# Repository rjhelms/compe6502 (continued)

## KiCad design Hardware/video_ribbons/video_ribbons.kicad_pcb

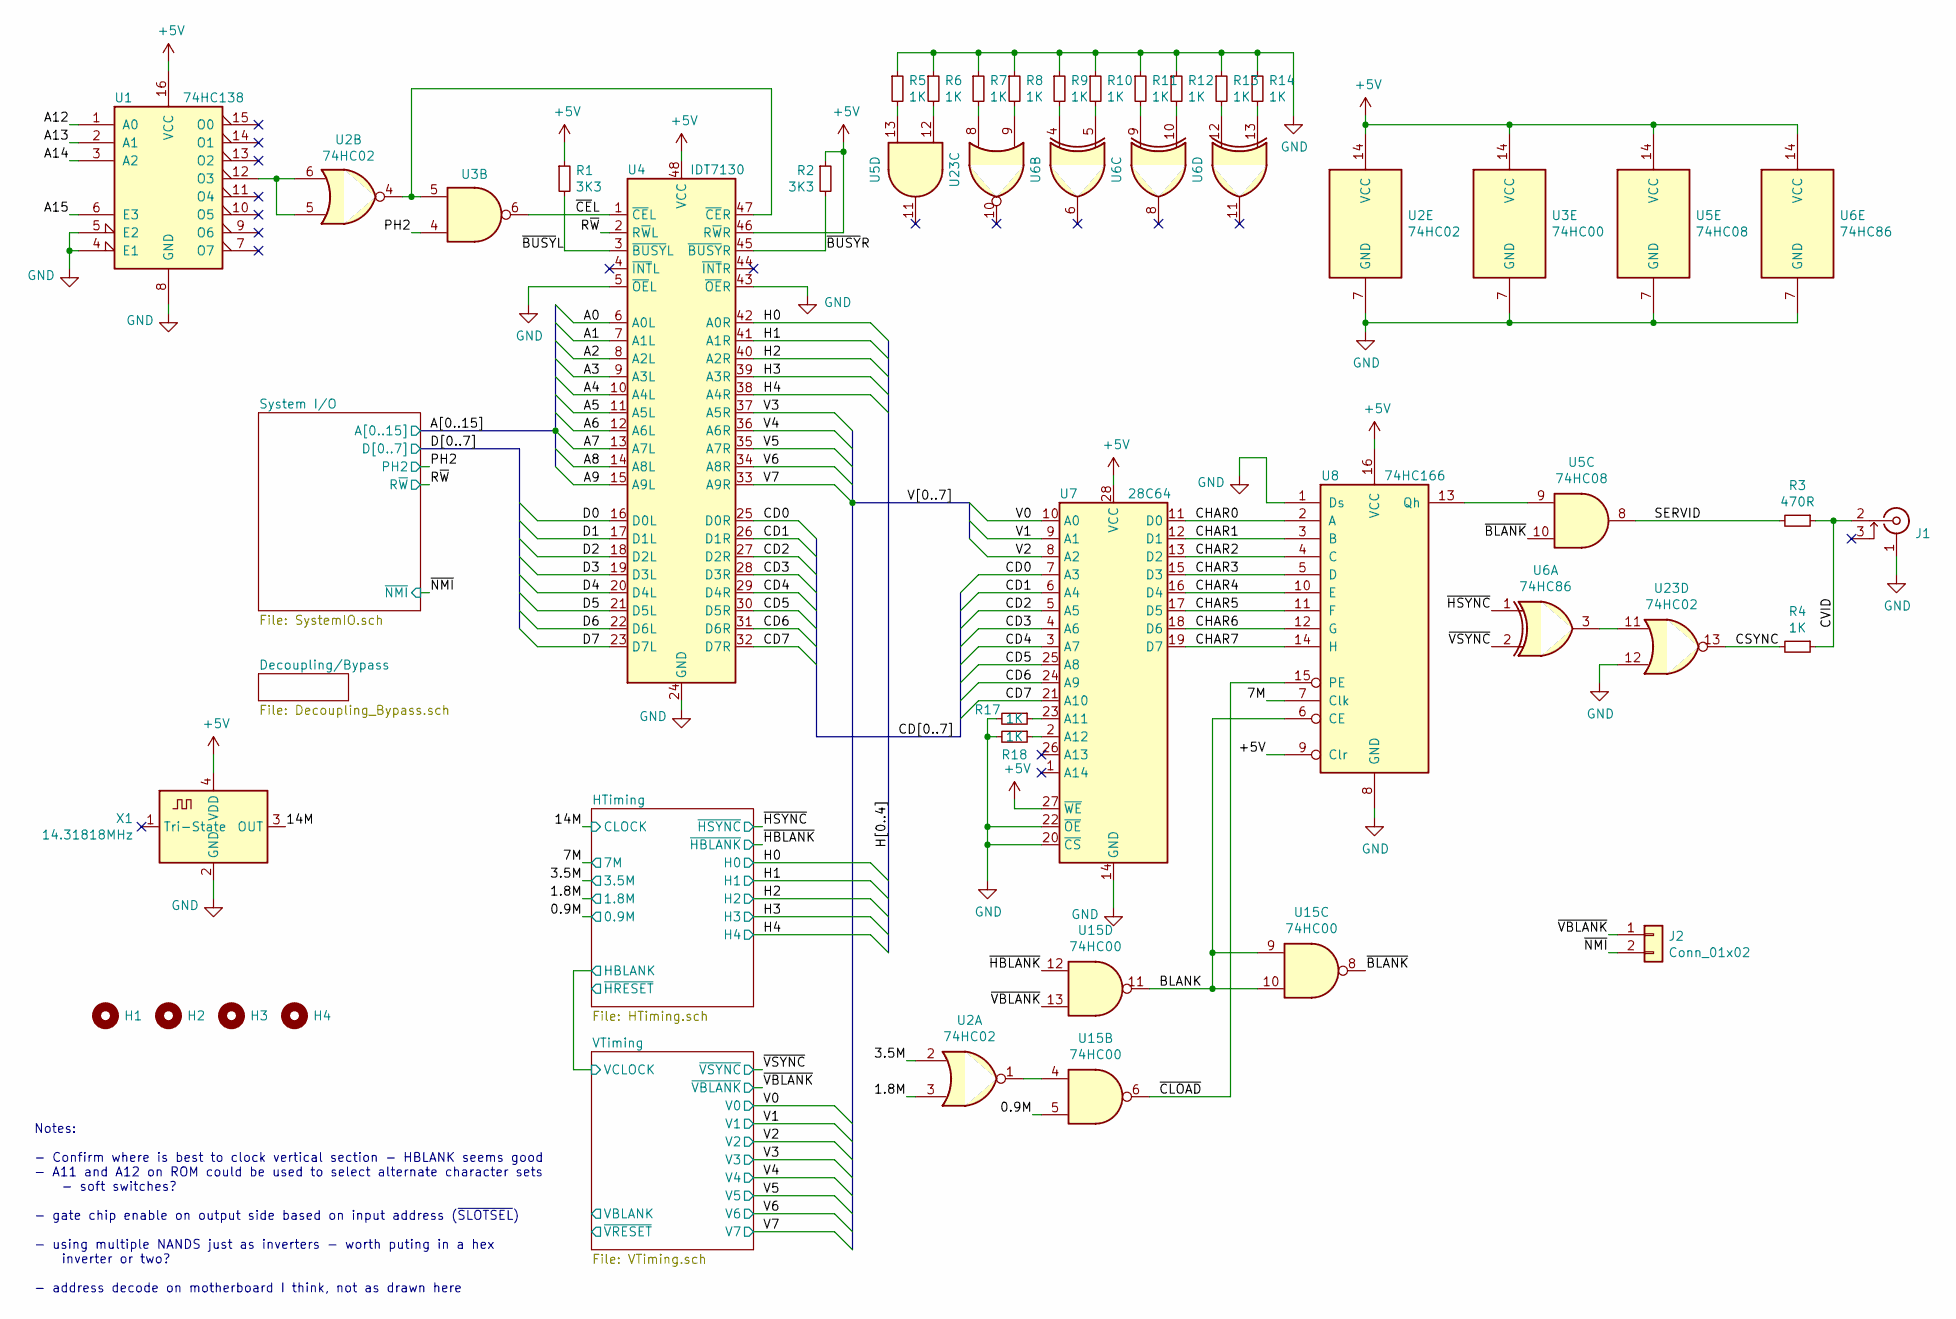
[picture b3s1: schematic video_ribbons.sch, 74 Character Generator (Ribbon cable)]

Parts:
H1, H2, H3, H4: MountingHole; MountingHole_3.2mm_M3
J1: Conn_Coaxial_Sleeve_Pin2Tip; Jack_RCA_Switchcraft_PJRAN1X1UxxX
J2: Conn_01x02; PinHeader_1x02_P2.54mm_Vertical
R1, R2: 3K3; R_0805_2012Metric
R3: 470R; R_0805_2012Metric
R4, R5, R6, R7, R8, R9, R10, R11, R12, R13, R14, R17, R18: 1K; R_0805_2012Metric
U1: 74HC138; SOIC-16_3.9x9.9mm_P1.27mm
U2, U23: 74HC02; SOIC-14_3.9x8.7mm_P1.27mm
U3, U15: 74HC00; SOIC-14_3.9x8.7mm_P1.27mm
U4: IDT7130; DIP-48_W15.24mm_Socket_LongPads
U5: 74HC08; SOIC-14_3.9x8.7mm_P1.27mm
U6: 74HC86; SOIC-14_3.9x8.7mm_P1.27mm
U7: 28C64; DIP-28_W15.24mm_Socket_LongPads
U8: 74HC166; SOIC-16_3.9x9.9mm_P1.27mm
X1: 14.31818MHz; Oscillator_SMD_IQD_IQXO70-4Pin_7.5x5.0mm

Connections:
+5V: R1.1, R2.1, U1.16 (VCC), U2.14 (VCC), U3.14 (VCC), U4.46 (R~W~R), U4.48 (VCC), U5.14 (VCC), U6.14 (VCC), U7.27 (~WE), U7.28 (VCC), U8.9 (Clr), U8.16 (VCC), X1.4 (VDD); also elsewhere on the board
/0.9M: U15.5; also elsewhere on the board
/1.8M: U2.3; also elsewhere on the board
/3.5M: U2.2; also elsewhere on the board
/7M: U8.7 (Clk); also elsewhere on the board
/14M: X1.3 (OUT); also elsewhere on the board
/A0: U4.6 (A0L); also elsewhere on the board
/A1: U4.7 (A1L); also elsewhere on the board
/A2: U4.8 (A2L); also elsewhere on the board
/A3: U4.9 (A3L); also elsewhere on the board
/A4: U4.10 (A4L); also elsewhere on the board
/A5: U4.11 (A5L); also elsewhere on the board
/A6: U4.12 (A6L); also elsewhere on the board
/A7: U4.13 (A7L); also elsewhere on the board
/A8: U4.14 (A8L); also elsewhere on the board
/A9: U4.15 (A9L); also elsewhere on the board
/A12: U1.1 (A0); also elsewhere on the board
/A13: U1.2 (A1); also elsewhere on the board
/A14: U1.3 (A2); also elsewhere on the board
/A15: U1.6 (E3); also elsewhere on the board
/BLANK: U8.6 (CE), U15.9, U15.10, U15.11
/CD0: U4.25 (D0R), U7.7 (A3)
/CD1: U4.26 (D1R), U7.6 (A4)
/CD2: U4.27 (D2R), U7.5 (A5)
/CD3: U4.28 (D3R), U7.4 (A6)
/CD4: U4.29 (D4R), U7.3 (A7)
/CD5: U4.30 (D5R), U7.25 (A8)
/CD6: U4.31 (D6R), U7.24 (A9)
/CD7: U4.32 (D7R), U7.21 (A10)
/CHAR0: U7.11 (D0), U8.2 (A)
/CHAR1: U7.12 (D1), U8.3 (B)
/CHAR2: U7.13 (D2), U8.4 (C)
/CHAR3: U7.15 (D3), U8.5 (D)
/CHAR4: U7.16 (D4), U8.10 (E)
/CHAR5: U7.17 (D5), U8.11 (F)
/CHAR6: U7.18 (D6), U8.12 (G)
/CHAR7: U7.19 (D7), U8.14 (H)
/CSYNC: R4.2, U23.13
/CVID: J1.2 (In), R3.1, R4.1
/D0: U4.16 (D0L); also elsewhere on the board
/D1: U4.17 (D1L); also elsewhere on the board
/D2: U4.18 (D2L); also elsewhere on the board
/D3: U4.19 (D3L); also elsewhere on the board
/D4: U4.20 (D4L); also elsewhere on the board
/D5: U4.21 (D5L); also elsewhere on the board
/D6: U4.22 (D6L); also elsewhere on the board
/D7: U4.23 (D7L); also elsewhere on the board
/H0: U4.42 (A0R); also elsewhere on the board
/H1: U4.41 (A1R); also elsewhere on the board
/H2: U4.40 (A2R); also elsewhere on the board
/H3: U4.39 (A3R); also elsewhere on the board
/H4: U4.38 (A4R); also elsewhere on the board
/PH2: U3.4; also elsewhere on the board
/R~W: U4.2 (R~W~L); also elsewhere on the board
/SERVID: R3.2, U5.8
/V0: U7.10 (A0); also elsewhere on the board
/V1: U7.9 (A1); also elsewhere on the board
/V2: U7.8 (A2); also elsewhere on the board
/V3: U4.37 (A5R); also elsewhere on the board
/V4: U4.36 (A6R); also elsewhere on the board
/V5: U4.35 (A7R); also elsewhere on the board
/V6: U4.34 (A8R); also elsewhere on the board
/V7: U4.33 (A9R); also elsewhere on the board
/~BLANK: U5.10, U15.8
/~BUSY~L: R1.2, U4.3 (~BUSY~L)
/~BUSY~R: R2.2, U4.45 (~BUSY~R)
/~CE~L: U3.6, U4.1 (~CE~L)
/~CLOAD: U8.15 (PE), U15.6
/~HBLANK: U15.12; also elsewhere on the board
/~HSYNC: U6.1; also elsewhere on the board
/~NMI: J2.2; also elsewhere on the board
/~VBLANK: J2.1, U15.13; also elsewhere on the board
/~VSYNC: U6.2; also elsewhere on the board
GND: J1.1 (Ext), R5.1, R6.1, R7.1, R8.1, R9.1, R10.1, R11.1, R12.1, R13.1, R14.1, R17.2, R18.2, U1.4 (E1), U1.5 (E2), U1.8 (GND), U2.7 (GND), U3.7 (GND), U4.5 (~OE~L), U4.24 (GND), U4.43 (~OE~R), U5.7 (GND), U6.7 (GND), U7.14 (GND), U7.20 (~CS), U7.22 (~OE), U8.1 (Ds), U8.8 (GND), U23.12, X1.2 (GND); also elsewhere on the board
unnamed: R5.2, U5.13
unnamed: R6.2, U5.12
unnamed: R7.2, U23.8
unnamed: R8.2, U23.9
unnamed: R9.2, U6.4
unnamed: R10.2, U6.5
unnamed: R11.2, U6.9
unnamed: R12.2, U6.10
unnamed: R13.2, U6.12
unnamed: R14.2, U6.13
unnamed: R17.1, U7.23 (A11)
unnamed: R18.1, U7.2 (A12)
unnamed: U1.12 (O3), U2.5, U2.6
unnamed: U2.4, U3.5, U4.47 (~CE~R)
unnamed: U5.9, U8.13 (Qh)
unnamed: U2.1, U15.4
unnamed: U6.3, U23.11

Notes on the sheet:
Notes: - Confirm where is best to clock vertical section - HBLANK seems good - A11 and A12 on ROM could be used to select alternate character sets - soft switches? - gate chip enable on output side based on input address (~SLOTSEL~) - using multiple NANDS just as inverters - worth puting in a hex i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

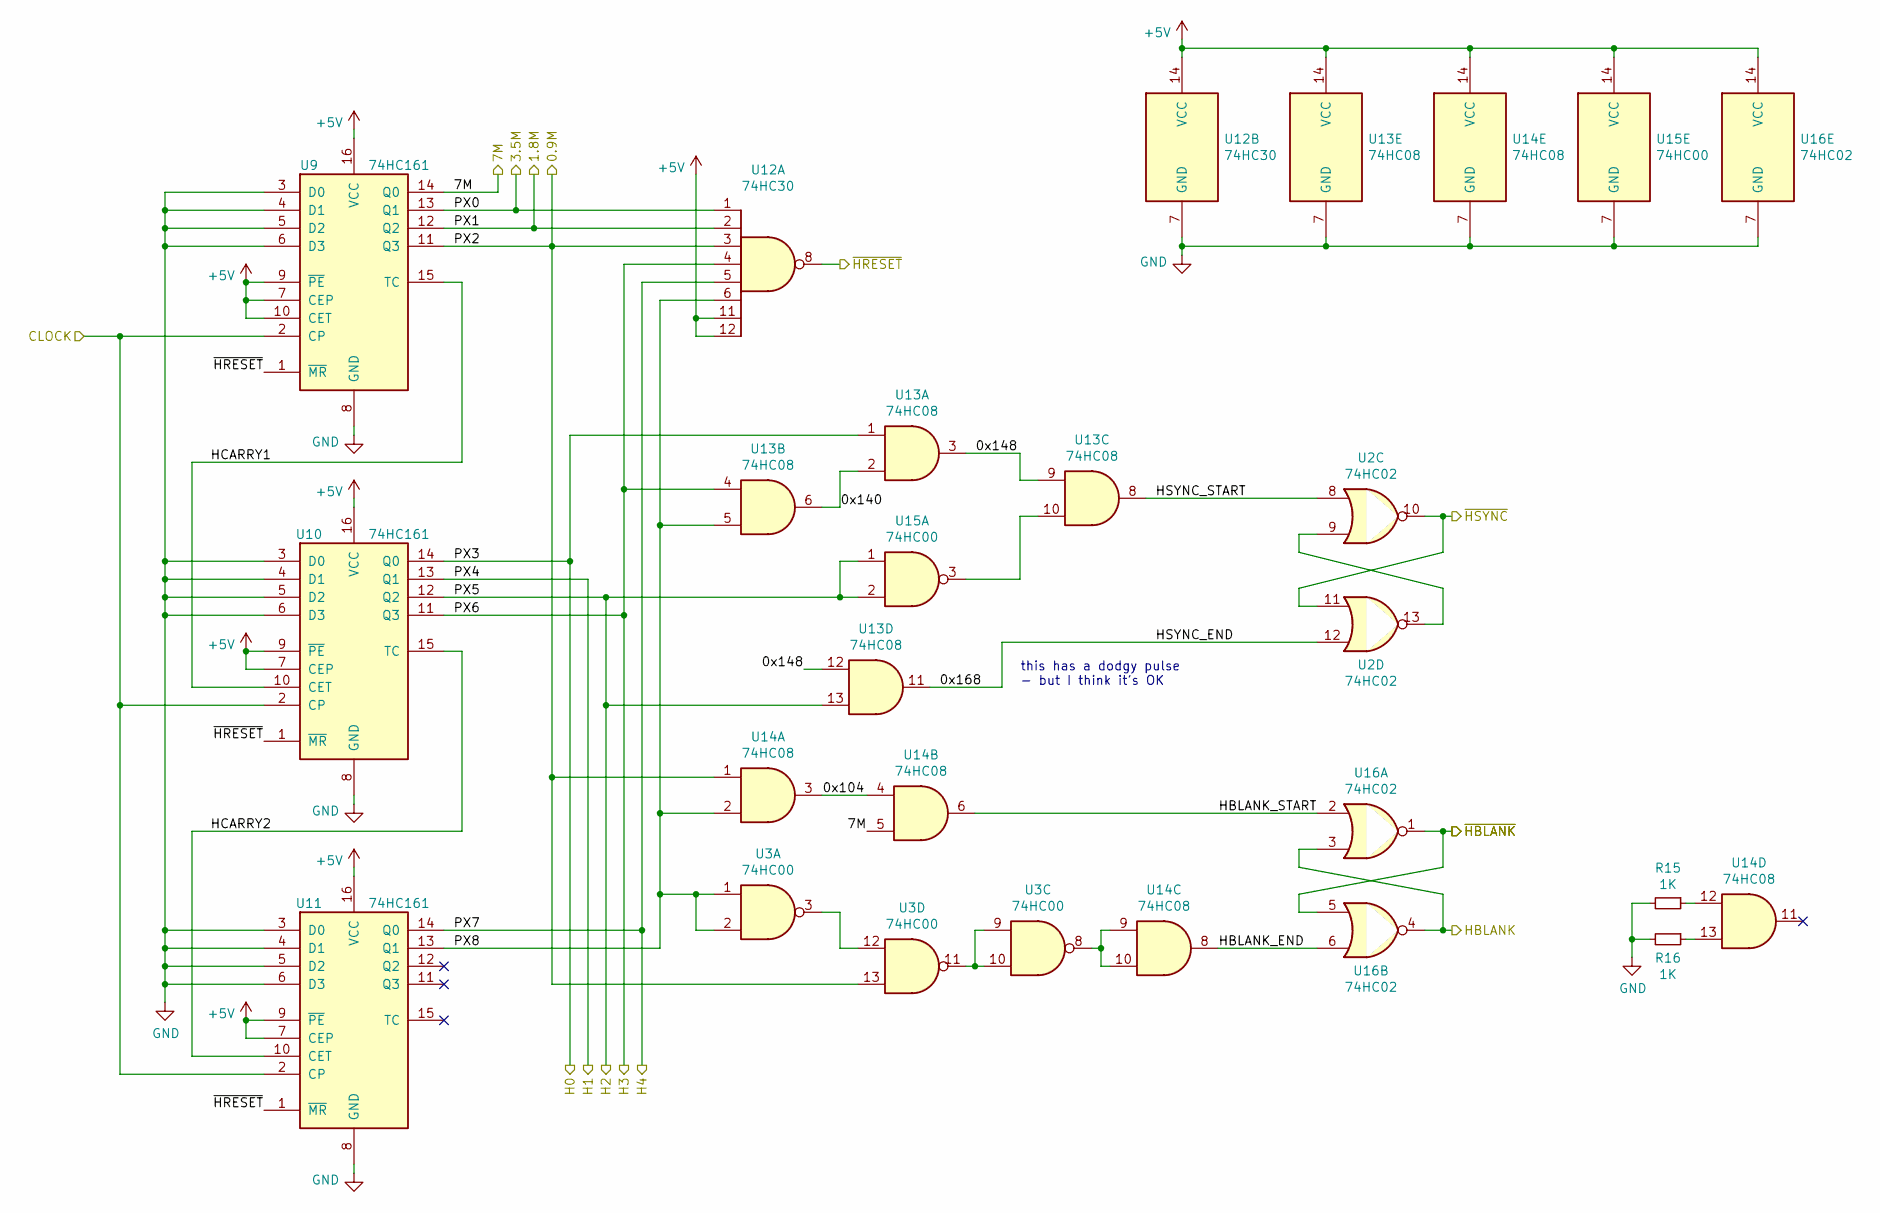
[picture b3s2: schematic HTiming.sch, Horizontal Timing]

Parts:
R15, R16: 1K; R_0805_2012Metric
U2, U16: 74HC02; SOIC-14_3.9x8.7mm_P1.27mm
U3, U15: 74HC00; SOIC-14_3.9x8.7mm_P1.27mm
U9, U10, U11: 74HC161; SOIC-16_3.9x9.9mm_P1.27mm
U12: 74HC30; SOIC-14_3.9x8.7mm_P1.27mm
U13, U14: 74HC08; SOIC-14_3.9x8.7mm_P1.27mm

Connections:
+5V: U9.7 (CEP), U9.9 (~PE), U9.10 (CET), U9.16 (VCC), U10.7 (CEP), U10.9 (~PE), U10.16 (VCC), U11.7 (CEP), U11.9 (~PE), U11.16 (VCC), U12.11, U12.12, U12.14 (VCC), U13.14 (VCC), U14.14 (VCC), U15.14 (VCC), U16.14 (VCC); also elsewhere on the board
/0.9M: U3.13, U9.11 (Q3), U12.3, U14.1; also elsewhere on the board
/1.8M: U9.12 (Q2), U12.2; also elsewhere on the board
/3.5M: U9.13 (Q1), U12.1; also elsewhere on the board
/7M: U9.14 (Q0), U14.5; also elsewhere on the board
/14M: U9.2 (CP), U10.2 (CP), U11.2 (CP); also elsewhere on the board
/H0: U10.14 (Q0), U13.1; also elsewhere on the board
/H1: U10.13 (Q1); also elsewhere on the board
/H2: U10.12 (Q2), U13.13, U15.1, U15.2; also elsewhere on the board
/H3: U10.11 (Q3), U12.4, U13.4; also elsewhere on the board
/H4: U11.14 (Q0), U12.5; also elsewhere on the board
/HTiming/0x104: U14.3, U14.4
/HTiming/0x140: U13.2, U13.6
/HTiming/0x148: U13.3, U13.9, U13.12
/HTiming/0x168: U2.12, U13.11
/HTiming/HBLANK: U16.3, U16.4; also elsewhere on the board
/HTiming/HBLANK_END: U14.8, U16.6
/HTiming/HBLANK_START: U14.6, U16.2
/HTiming/HCARRY1: U9.15 (TC), U10.10 (CET)
/HTiming/HCARRY2: U10.15 (TC), U11.10 (CET)
/HTiming/HSYNC_START: U2.8, U13.8
/HTiming/PX8: U3.1, U3.2, U11.13 (Q1), U12.6, U13.5, U14.2
/HTiming/~HRESET: U9.1 (~MR), U10.1 (~MR), U11.1 (~MR), U12.8
/~HBLANK: U16.1, U16.5; also elsewhere on the board
/~HSYNC: U2.10, U2.11; also elsewhere on the board
GND: R15.2, R16.2, U9.3 (D0), U9.4 (D1), U9.5 (D2), U9.6 (D3), U9.8 (GND), U10.3 (D0), U10.4 (D1), U10.5 (D2), U10.6 (D3), U10.8 (GND), U11.3 (D0), U11.4 (D1), U11.5 (D2), U11.6 (D3), U11.8 (GND), U12.7 (GND), U13.7 (GND), U14.7 (GND), U15.7 (GND), U16.7 (GND); also elsewhere on the board
unnamed: R15.1, U14.12
unnamed: R16.1, U14.13
unnamed: U2.9, U2.13
unnamed: U3.9, U3.10, U3.11
unnamed: U3.3, U3.12
unnamed: U13.10, U15.3
unnamed: U3.8, U14.9, U14.10

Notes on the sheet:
this has a dodgy pulse - but I think it's OK

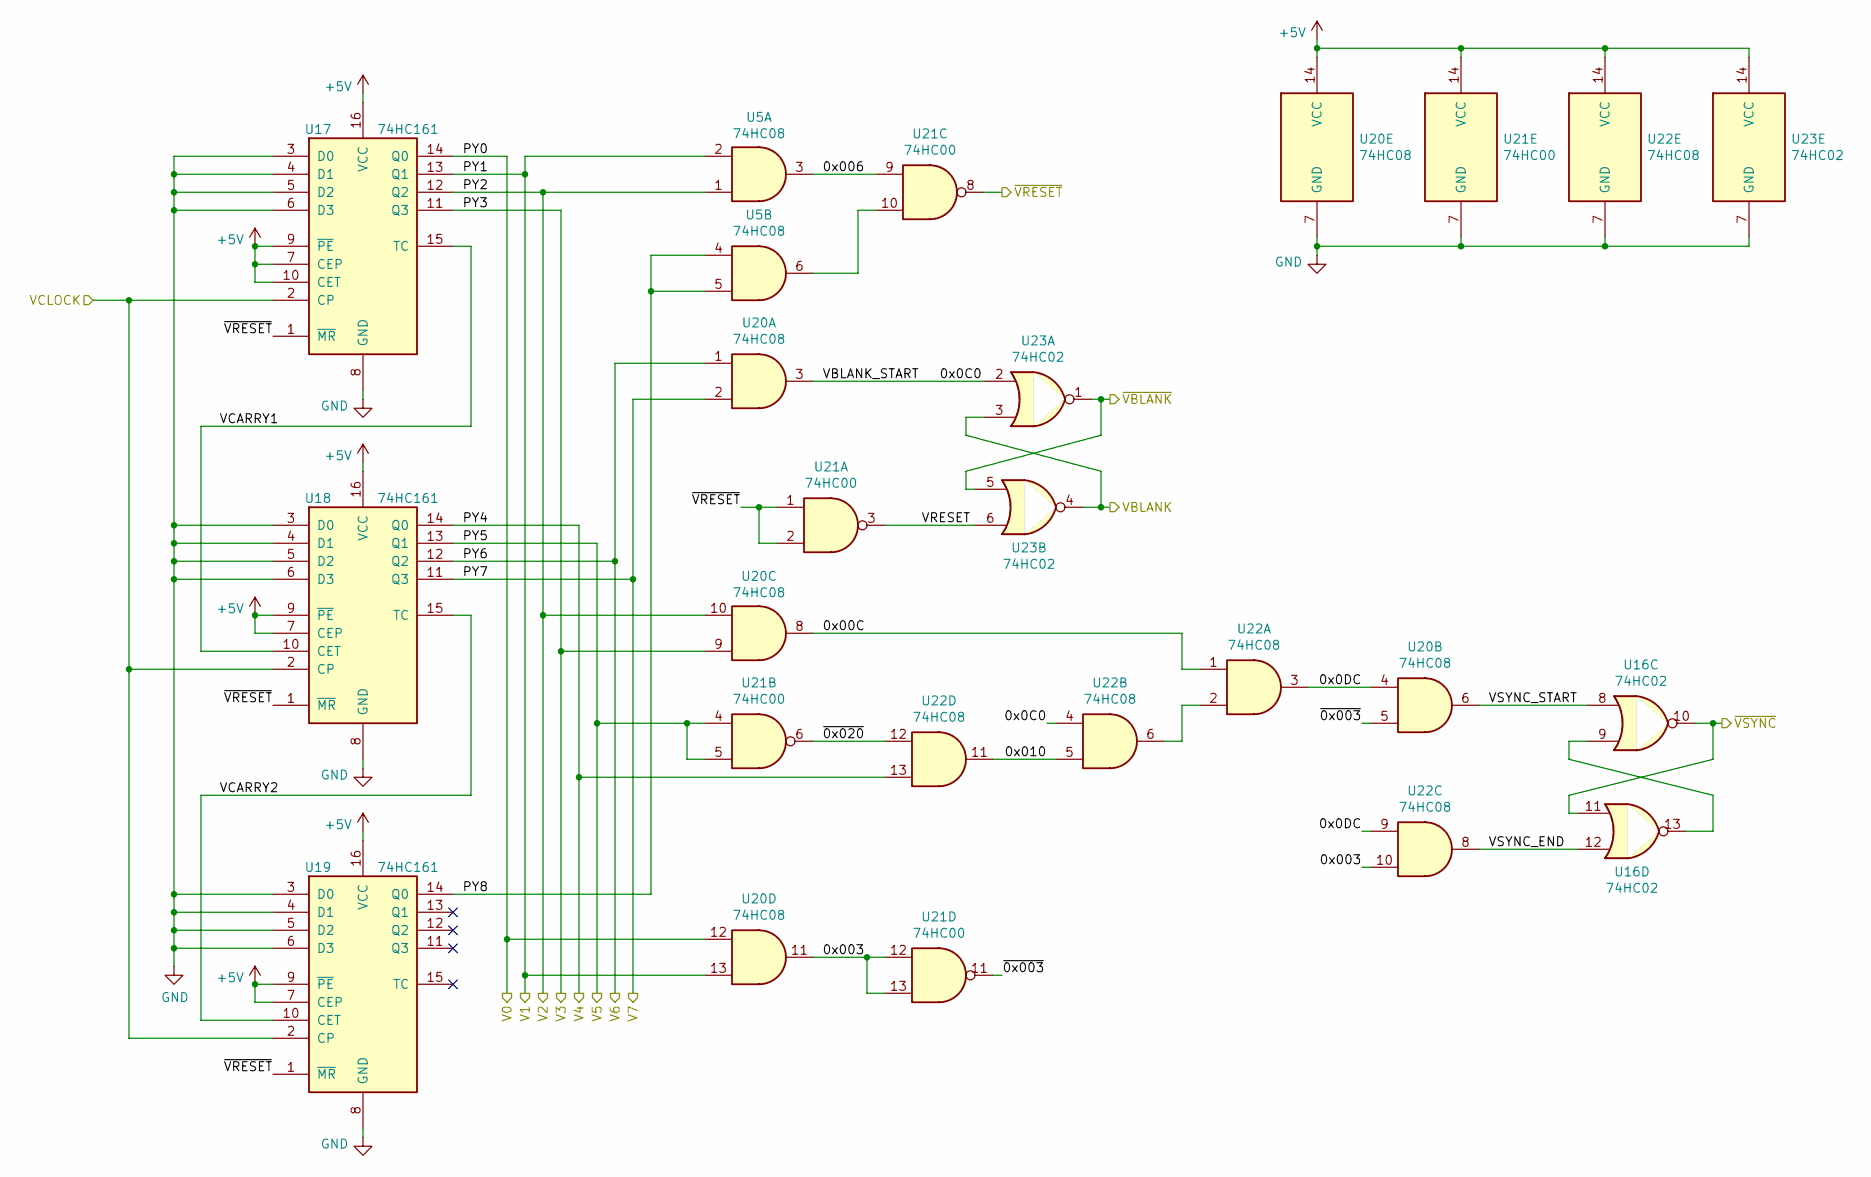
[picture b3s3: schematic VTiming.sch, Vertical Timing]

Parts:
U5, U20, U22: 74HC08; SOIC-14_3.9x8.7mm_P1.27mm
U16, U23: 74HC02; SOIC-14_3.9x8.7mm_P1.27mm
U17, U18, U19: 74HC161; SOIC-16_3.9x9.9mm_P1.27mm
U21: 74HC00; SOIC-14_3.9x8.7mm_P1.27mm

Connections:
+5V: U17.7 (CEP), U17.9 (~PE), U17.10 (CET), U17.16 (VCC), U18.7 (CEP), U18.9 (~PE), U18.16 (VCC), U19.7 (CEP), U19.9 (~PE), U19.16 (VCC), U20.14 (VCC), U21.14 (VCC), U22.14 (VCC), U23.14 (VCC); also elsewhere on the board
/HTiming/HBLANK: U17.2 (CP), U18.2 (CP), U19.2 (CP); also elsewhere on the board
/V0: U17.14 (Q0), U20.12; also elsewhere on the board
/V1: U5.2, U17.13 (Q1), U20.13; also elsewhere on the board
/V2: U5.1, U17.12 (Q2), U20.10; also elsewhere on the board
/V3: U17.11 (Q3), U20.9; also elsewhere on the board
/V4: U18.14 (Q0), U22.13; also elsewhere on the board
/V5: U18.13 (Q1), U21.4, U21.5; also elsewhere on the board
/V6: U18.12 (Q2), U20.1; also elsewhere on the board
/V7: U18.11 (Q3), U20.2; also elsewhere on the board
/VTiming/0x00C: U20.8, U22.1
/VTiming/0x0C0: U20.3, U22.4, U23.2
/VTiming/0x0DC: U20.4, U22.3, U22.9
/VTiming/0x003: U20.11, U21.12, U21.13, U22.10
/VTiming/0x006: U5.3, U21.9
/VTiming/0x010: U22.5, U22.11
/VTiming/PY8: U5.4, U5.5, U19.14 (Q0)
/VTiming/VBLANK: U23.3, U23.4
/VTiming/VCARRY1: U17.15 (TC), U18.10 (CET)
/VTiming/VCARRY2: U18.15 (TC), U19.10 (CET)
/VTiming/VRESET: U21.3, U23.6
/VTiming/VSYNC_END: U16.12, U22.8
/VTiming/VSYNC_START: U16.8, U20.6
/VTiming/~0x003: U20.5, U21.11
/VTiming/~0x020: U21.6, U22.12
/VTiming/~VRESET: U17.1 (~MR), U18.1 (~MR), U19.1 (~MR), U21.1, U21.2, U21.8
/~VBLANK: U23.1, U23.5; also elsewhere on the board
/~VSYNC: U16.10, U16.11; also elsewhere on the board
GND: U17.3 (D0), U17.4 (D1), U17.5 (D2), U17.6 (D3), U17.8 (GND), U18.3 (D0), U18.4 (D1), U18.5 (D2), U18.6 (D3), U18.8 (GND), U19.3 (D0), U19.4 (D1), U19.5 (D2), U19.6 (D3), U19.8 (GND), U20.7 (GND), U21.7 (GND), U22.7 (GND), U23.7 (GND); also elsewhere on the board
unnamed: U16.9, U16.13
unnamed: U5.6, U21.10
unnamed: U22.2, U22.6

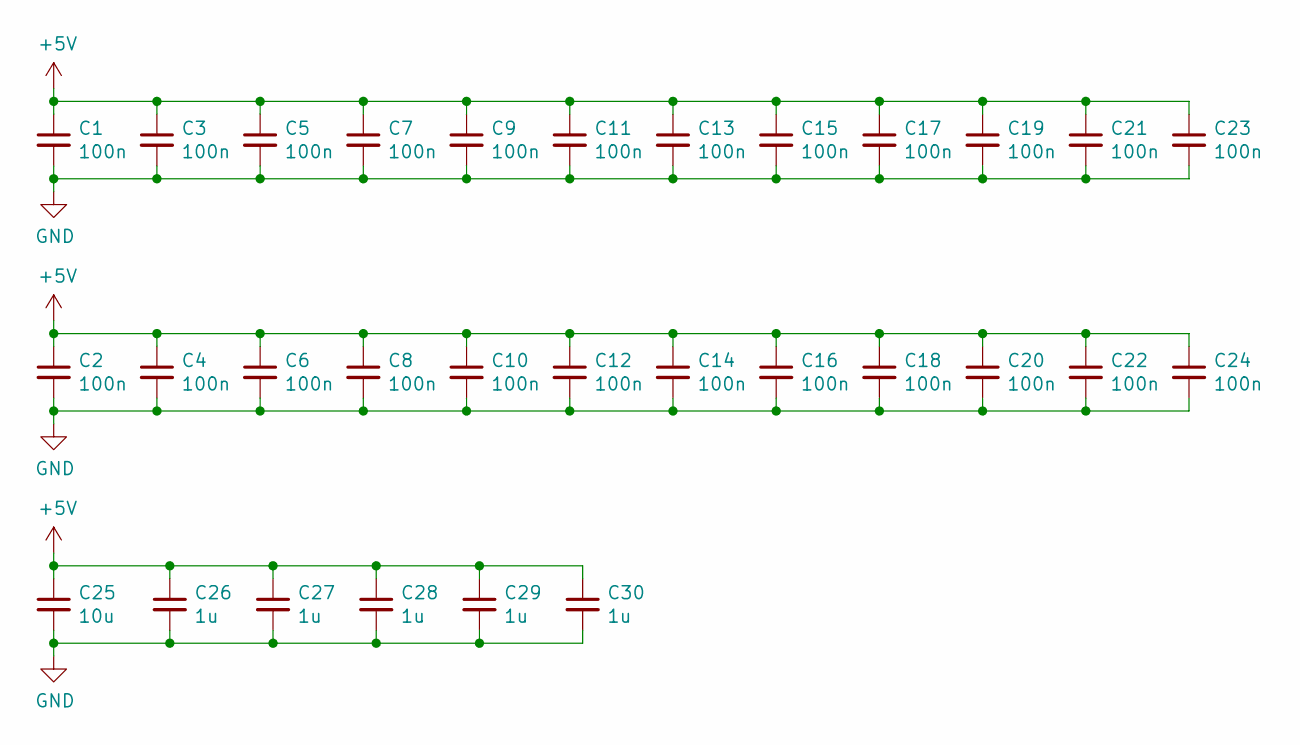
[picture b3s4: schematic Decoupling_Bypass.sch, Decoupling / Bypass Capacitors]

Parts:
C1, C2, C3, C4, C5, C6, C7, C8, C9, C10, C11, C12, C13, C14, C15, C16, C17, C18, C19, C20, C21, C22, C23, C24: 100n; C_0805_2012Metric
C25: 10u; C_0805_2012Metric
C26, C27, C28, C29, C30: 1u; C_0805_2012Metric

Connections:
+5V: C1.1, C2.1, C3.1, C4.1, C5.1, C6.1, C7.1, C8.1, C9.1, C10.1, C11.1, C12.1, C13.1, C14.1, C15.1, C16.1, C17.1, C18.1, C19.1, C20.1, C21.1, C22.1, C23.1, C24.1, C25.1, C26.1, C27.1, C28.1, C29.1, C30.1; also elsewhere on the board
GND: C1.2, C2.2, C3.2, C4.2, C5.2, C6.2, C7.2, C8.2, C9.2, C10.2, C11.2, C12.2, C13.2, C14.2, C15.2, C16.2, C17.2, C18.2, C19.2, C20.2, C21.2, C22.2, C23.2, C24.2, C25.2, C26.2, C27.2, C28.2, C29.2, C30.2; also elsewhere on the board

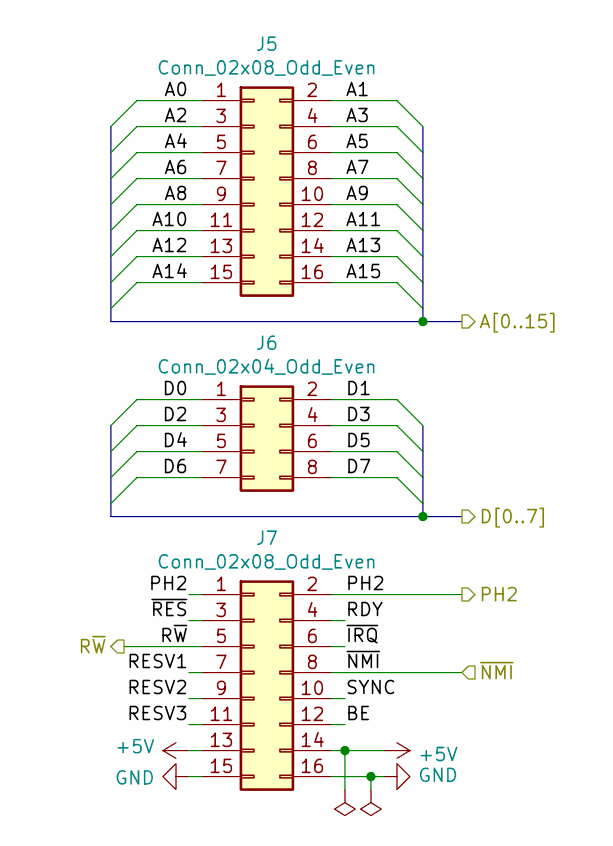
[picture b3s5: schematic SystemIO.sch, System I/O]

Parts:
J5, J7: Conn_02x08_Odd_Even; IDC-Header_2x08_P2.54mm_Vertical
J6: Conn_02x04_Odd_Even; IDC-Header_2x04_P2.54mm_Vertical

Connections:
+5V: J7.13, J7.14; also elsewhere on the board
/A0: J5.1; also elsewhere on the board
/A1: J5.2; also elsewhere on the board
/A2: J5.3; also elsewhere on the board
/A3: J5.4; also elsewhere on the board
/A4: J5.5; also elsewhere on the board
/A5: J5.6; also elsewhere on the board
/A6: J5.7; also elsewhere on the board
/A7: J5.8; also elsewhere on the board
/A8: J5.9; also elsewhere on the board
/A9: J5.10; also elsewhere on the board
/A12: J5.13; also elsewhere on the board
/A13: J5.14; also elsewhere on the board
/A14: J5.15; also elsewhere on the board
/A15: J5.16; also elsewhere on the board
/D0: J6.1; also elsewhere on the board
/D1: J6.2; also elsewhere on the board
/D2: J6.3; also elsewhere on the board
/D3: J6.4; also elsewhere on the board
/D4: J6.5; also elsewhere on the board
/D5: J6.6; also elsewhere on the board
/D6: J6.7; also elsewhere on the board
/D7: J6.8; also elsewhere on the board
/PH2: J7.1, J7.2; also elsewhere on the board
/R~W: J7.5; also elsewhere on the board
/System I/O/A10: J5.11
/System I/O/A11: J5.12
/System I/O/BE: J7.12
/System I/O/RDY: J7.4
/System I/O/RESV1: J7.7
/System I/O/RESV2: J7.9
/System I/O/RESV3: J7.11
/System I/O/SYNC: J7.10
/System I/O/~IRQ: J7.6
/System I/O/~RES: J7.3
/~NMI: J7.8; also elsewhere on the board
GND: J7.15, J7.16; also elsewhere on the board

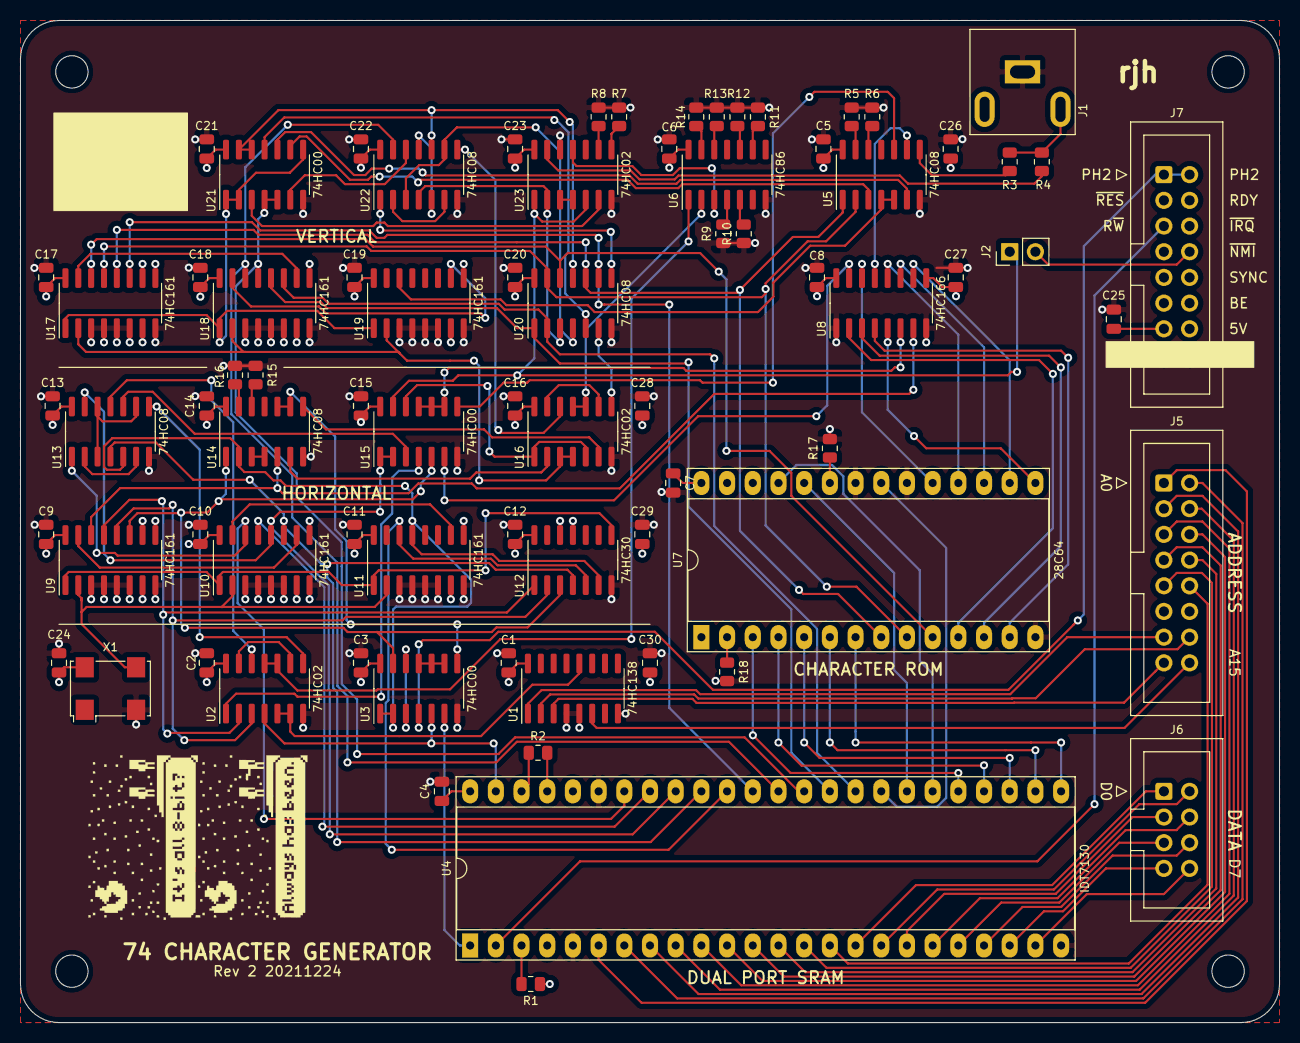
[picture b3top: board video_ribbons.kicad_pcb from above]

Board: 4 copper layers, 124.5 x 99.1 mm, 81 parts (0 on the bottom side), 129 nets.

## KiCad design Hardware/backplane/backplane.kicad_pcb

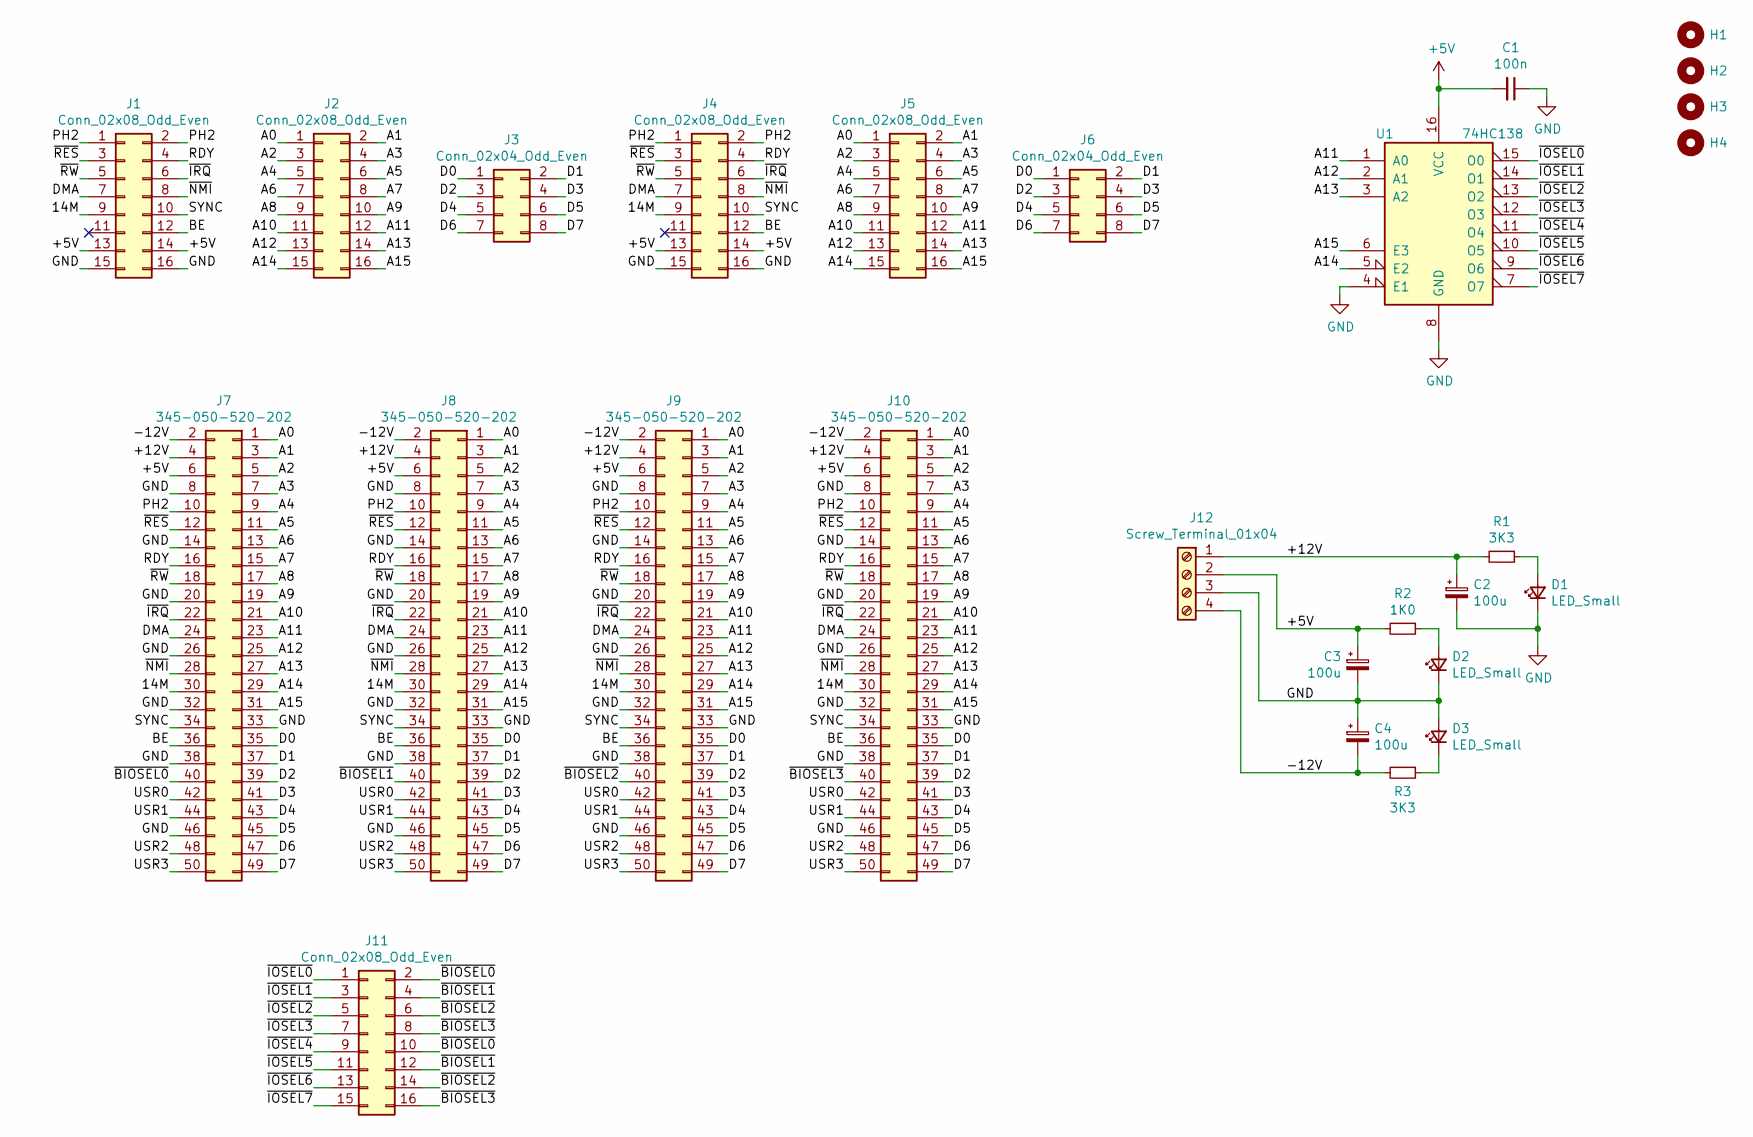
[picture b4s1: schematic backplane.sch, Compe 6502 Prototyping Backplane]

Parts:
C1: 100n; C_Disc_D5.0mm_W2.5mm_P2.50mm; MPN K104K15X7RF5TL2
C2, C3, C4: 100u; CP_Radial_D6.3mm_P2.50mm; MPN 860020573008
D1, D2, D3: LED_Small; LED_D5.0mm; MPN SLR-56MG3F
H1, H2, H3, H4: MountingHole; MountingHole_3.2mm_M3
J1, J2, J4, J5: Conn_02x08_Odd_Even; IDC-Header_2x08_P2.54mm_Vertical; MPN 302-S161
J3, J6: Conn_02x04_Odd_Even; IDC-Header_2x04_P2.54mm_Vertical; MPN 75869-132LF
J7, J8, J9, J10: 345-050-520-202; EDAC_345-050-520-202; MPN 345-050-520-202
J11: Conn_02x08_Odd_Even; PinHeader_2x08_P2.54mm_Vertical
J12: Screw_Terminal_01x04; TerminalBlock_Phoenix_PT-1,5-4-3.5-H_1x04_P3.50mm_Horizontal; MPN 1984633
R1, R3: 3K3; R_Axial_DIN0207_L6.3mm_D2.5mm_P7.62mm_Horizontal; MPN CF14JT3K30
R2: 1K0; R_Axial_DIN0207_L6.3mm_D2.5mm_P7.62mm_Horizontal; MPN CF14JT1K00
U1: 74HC138; DIP-16_W7.62mm_LongPads; MPN SN74HC138N

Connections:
+5V: C1.2, C3.1, J1.13, J1.14, J4.13, J4.14, J7.6, J8.6, J9.6, J10.6, J12.2, R2.2, U1.16 (VCC)
/14M: J1.9, J4.9, J7.30, J8.30, J9.30, J10.30
/+12V: C2.1, J7.4, J8.4, J9.4, J10.4, J12.1, R1.2
/-12V: C4.2, J7.2, J8.2, J9.2, J10.2, J12.4, R3.2
/A0: J2.1, J5.1, J7.1, J8.1, J9.1, J10.1
/A1: J2.2, J5.2, J7.3, J8.3, J9.3, J10.3
/A2: J2.3, J5.3, J7.5, J8.5, J9.5, J10.5
/A3: J2.4, J5.4, J7.7, J8.7, J9.7, J10.7
/A4: J2.5, J5.5, J7.9, J8.9, J9.9, J10.9
/A5: J2.6, J5.6, J7.11, J8.11, J9.11, J10.11
/A6: J2.7, J5.7, J7.13, J8.13, J9.13, J10.13
/A7: J2.8, J5.8, J7.15, J8.15, J9.15, J10.15
/A8: J2.9, J5.9, J7.17, J8.17, J9.17, J10.17
/A9: J2.10, J5.10, J7.19, J8.19, J9.19, J10.19
/A10: J2.11, J5.11, J7.21, J8.21, J9.21, J10.21
/A11: J2.12, J5.12, J7.23, J8.23, J9.23, J10.23, U1.1 (A0)
/A12: J2.13, J5.13, J7.25, J8.25, J9.25, J10.25, U1.2 (A1)
/A13: J2.14, J5.14, J7.27, J8.27, J9.27, J10.27, U1.3 (A2)
/A14: J2.15, J5.15, J7.29, J8.29, J9.29, J10.29, U1.5 (E2)
/A15: J2.16, J5.16, J7.31, J8.31, J9.31, J10.31, U1.6 (E3)
/BE: J1.12, J4.12, J7.36, J8.36, J9.36, J10.36
/D0: J3.1, J6.1, J7.35, J8.35, J9.35, J10.35
/D1: J3.2, J6.2, J7.37, J8.37, J9.37, J10.37
/D2: J3.3, J6.3, J7.39, J8.39, J9.39, J10.39
/D3: J3.4, J6.4, J7.41, J8.41, J9.41, J10.41
/D4: J3.5, J6.5, J7.43, J8.43, J9.43, J10.43
/D5: J3.6, J6.6, J7.45, J8.45, J9.45, J10.45
/D6: J3.7, J6.7, J7.47, J8.47, J9.47, J10.47
/D7: J3.8, J6.8, J7.49, J8.49, J9.49, J10.49
/DMA: J1.7, J4.7, J7.24, J8.24, J9.24, J10.24
/PH2: J1.1, J1.2, J4.1, J4.2, J7.10, J8.10, J9.10, J10.10
/RDY: J1.4, J4.4, J7.16, J8.16, J9.16, J10.16
/SYNC: J1.10, J4.10, J7.34, J8.34, J9.34, J10.34
/USR0: J7.42, J8.42, J9.42, J10.42
/USR1: J7.44, J8.44, J9.44, J10.44
/USR2: J7.48, J8.48, J9.48, J10.48
/USR3: J7.50, J8.50, J9.50, J10.50
/~BIOSEL0: J7.40, J11.2, J11.10
/~BIOSEL1: J8.40, J11.4, J11.12
/~BIOSEL2: J9.40, J11.6, J11.14
/~BIOSEL3: J10.40, J11.8, J11.16
/~IOSEL0: J11.1, U1.15 (O0)
/~IOSEL1: J11.3, U1.14 (O1)
/~IOSEL2: J11.5, U1.13 (O2)
/~IOSEL3: J11.7, U1.12 (O3)
/~IOSEL4: J11.9, U1.11 (O4)
/~IOSEL5: J11.11, U1.10 (O5)
/~IOSEL6: J11.13, U1.9 (O6)
/~IOSEL7: J11.15, U1.7 (O7)
/~IRQ: J1.6, J4.6, J7.22, J8.22, J9.22, J10.22
/~NMI: J1.8, J4.8, J7.28, J8.28, J9.28, J10.28
/~RES: J1.3, J4.3, J7.12, J8.12, J9.12, J10.12
/~RW: J1.5, J4.5, J7.18, J8.18, J9.18, J10.18
GND: C1.1, C2.2, C3.2, C4.1, D1.1 (K), D2.1 (K), D3.2 (A), J1.15, J1.16, J4.15, J4.16, J7.8, J7.14, J7.20, J7.26, J7.32, J7.33, J7.38, J7.46, J8.8, J8.14, J8.20, J8.26, J8.32, J8.33, J8.38, J8.46, J9.8, J9.14, J9.20, J9.26, J9.32, J9.33, J9.38, J9.46, J10.8, J10.14, J10.20, J10.26, J10.32, J10.33, J10.38, J10.46, J12.3, U1.4 (E1), U1.8 (GND)
unnamed: D1.2 (A), R1.1
unnamed: D2.2 (A), R2.1
unnamed: D3.1 (K), R3.1

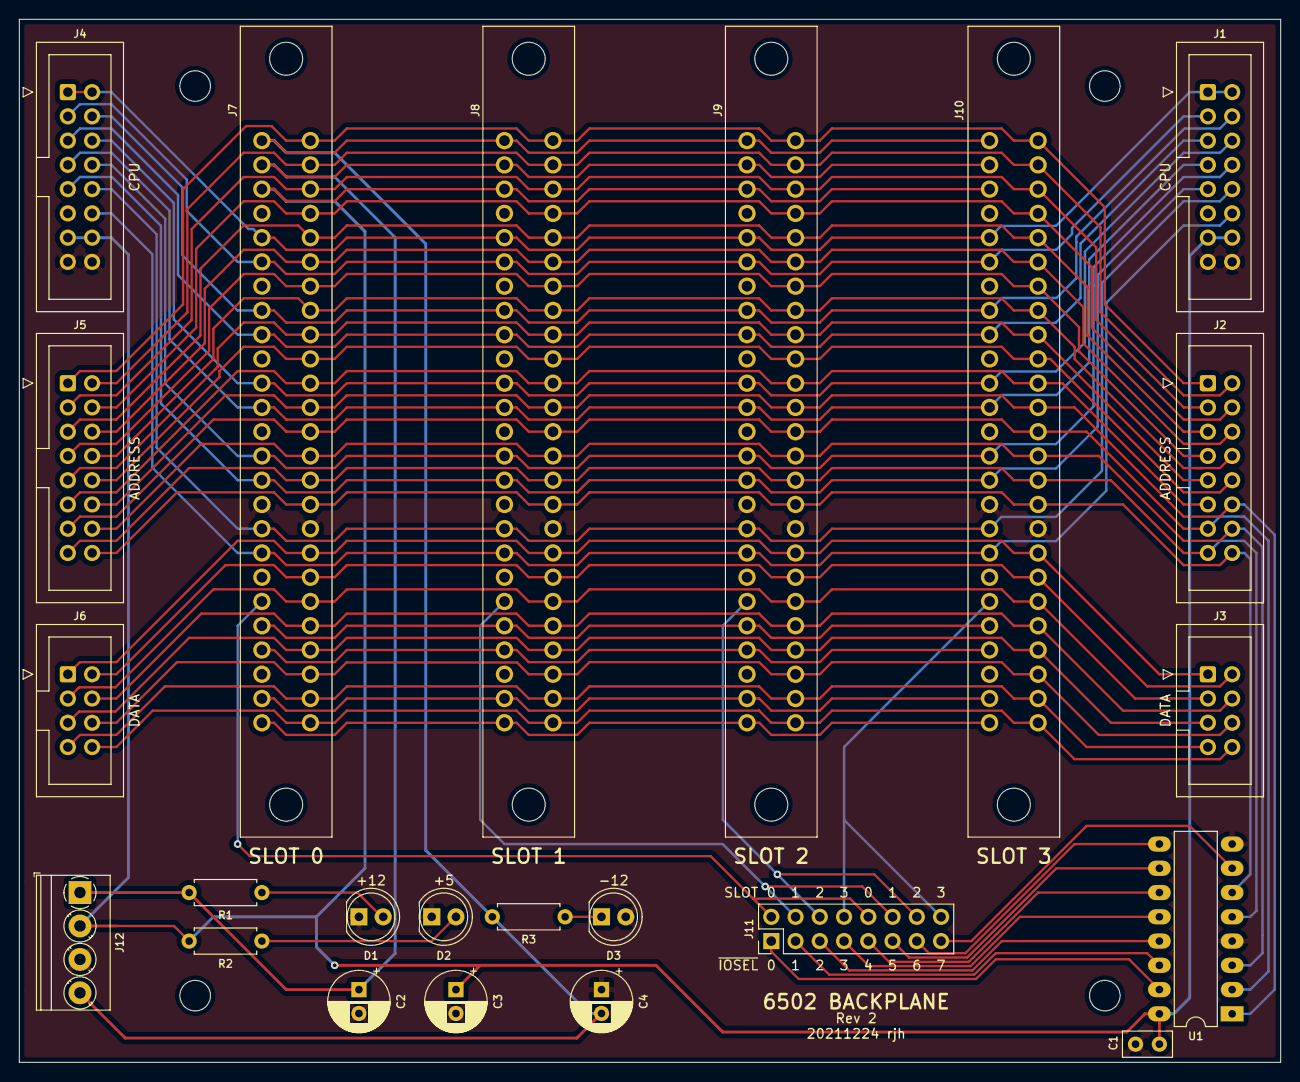
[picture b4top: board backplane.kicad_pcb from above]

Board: 2 copper layers, 132.1 x 109.2 mm, 27 parts (0 on the bottom side), 57 nets.
